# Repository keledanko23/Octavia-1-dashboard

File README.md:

# Octavia-1-Dashboard

A dashboard project.

## 📋 Project Overview

This is the Octavia-1 Dashboard - a comprehensive dashboard solution designed to use for pc simulators.
I have significantly expanded the scope of this project into a multi-phase hardware and software engineering build. I am converting a physical Skoda Octavia MK1 instrument cluster into a high-fidelity, real-time PC flight/racing simulator telemetry display.

## Current Progress (73 Hours Logged):

Hardware Reverse Engineering: Analyzed the internal trace lines, power rail limits, and motor pinouts of a replacement cluster following a previous hardware       failure (which was an excellent learning experience).
Interface Board Fabrication: Built a fully functional hardware interface on a 5x7cm barna perfboard, permanently soldering 3 driver ICs to safely handle logic     signal conversions between the microcontroller and the dashboard.
Complex Wire Harnessing: Engineered a point-to-point jumper wire harness to break out the connections. Applied hot-melt adhesive to insulate exposed solder        joints and provide mechanical strain relief.
Finished PCB design

## Remaining Scope:

Firmware Development: Writing custom python code using tkinter to simulate how it should work
Custom PCB Shield Design: Try to create a pcb for it.

## Diary

### 1st log (3.5 hours)
Analyzed the internal board layout of the replacement cluster. Traced the circuit lines to find the correct entry points for the stepper motors and indicators to avoid another hardware failure.
  ### Disassembly

  ### LEDS

  ### Pinout

## 2nd log (4 hours)
Mapped out the component placement on the 5x7cm barna perfboard. Positioned the three driver ICs and the male headers, then permanently soldered them onto the prototype board.

  ### ICs

## 3rd log (4.5 hours)
Started building the complex point-to-point jumper wire harness. Stripped, routed, and soldered individual wires from the IC legs to the breakout headers to safely transfer signals.

  ### Wires

## 4th log (4 hours)
Used a multimeter to test continuity on every single soldered connection. Checked for accidental solder bridges between the IC pins to prevent any short circuits before testing on live power.
 
  ### Checking

## 5th log (4 hours)
Completed the hardware prototyping phase. Applied layers of hot-melt adhesive over the wire cluster to insulate the exposed solder joints and provide mechanical strain relief against loose connections.

  ### Coating

## 6th log (5 hours)
Completed a simulation python code that shows how it will work.

  ### Python screenshot

  ## DEMO LINK: https://youtu.be/50QhlQHXBYw

  ## PYTHON CODE [HERE](https://github.com/keledanko23/Octavia-1-dashboard/blob/main/Octavia%20mk1%20dashboard%20python%20code.py)
  
  ## 7th log(2.5 hours)
  Started mapping out the pcb so i can recreate it later, added 1more led to the prototype, tried to add 2more but they burned out

  ## 8th log(9.2 hours)
  Started building the pcb outlines and holes, unfortunatly lot of the holes arent on their places where they should be even if i mesure 10 times, at least the outline is finally the form i need and some of the holes ar on their places.

## 9th log(3.7 hours)
Finaly got a chance to use a scaner to scan the pcb, imported it into kicad ad fixed al the kholes location and the form of the pcb, the pcb form is now finished

## 10th log(7 hours)
Drawed the schematic, it was really hard because I did not find some IC-s and had to draw them myself, at first it had 56errors but i managed to fix it

## 11th log(9 hours)
Added the components and conected most of the traces but I can´t make it cleaner, and i ran the DRC it said it has 250 errors and 110 alerts so i have a lot of work to do.

## 12th log(9.2 hours)
Fixed the layout, changed some expensive IC-s to cheaper ones, almost finished

## 13th log(5.8 hours)
Finally finished the pcb, it´s ready for order

## PCB FILES [HERE](https://github.com/keledanko23/Octavia-1-dashboard/tree/main/PCB%20FILES)

## [BOM IN TABLE FOMRAT](https://docs.google.com/spreadsheets/d/1glcknnUEBRp5D3enFJscNNNqzlTzyaNK3k0CQGIx504/edit?usp=sharing)

## 14th log(10,9 hours)
I soldered on evrything and foun out i got scammed and the ics from aliexpress were fake so i had to order new ones and found out my board had some issues so i will fix it in kicad
It is finished
## DEMO LINK: https://youtu.be/WoHd4EV55U8
**Last Updated:** October 30, 2026

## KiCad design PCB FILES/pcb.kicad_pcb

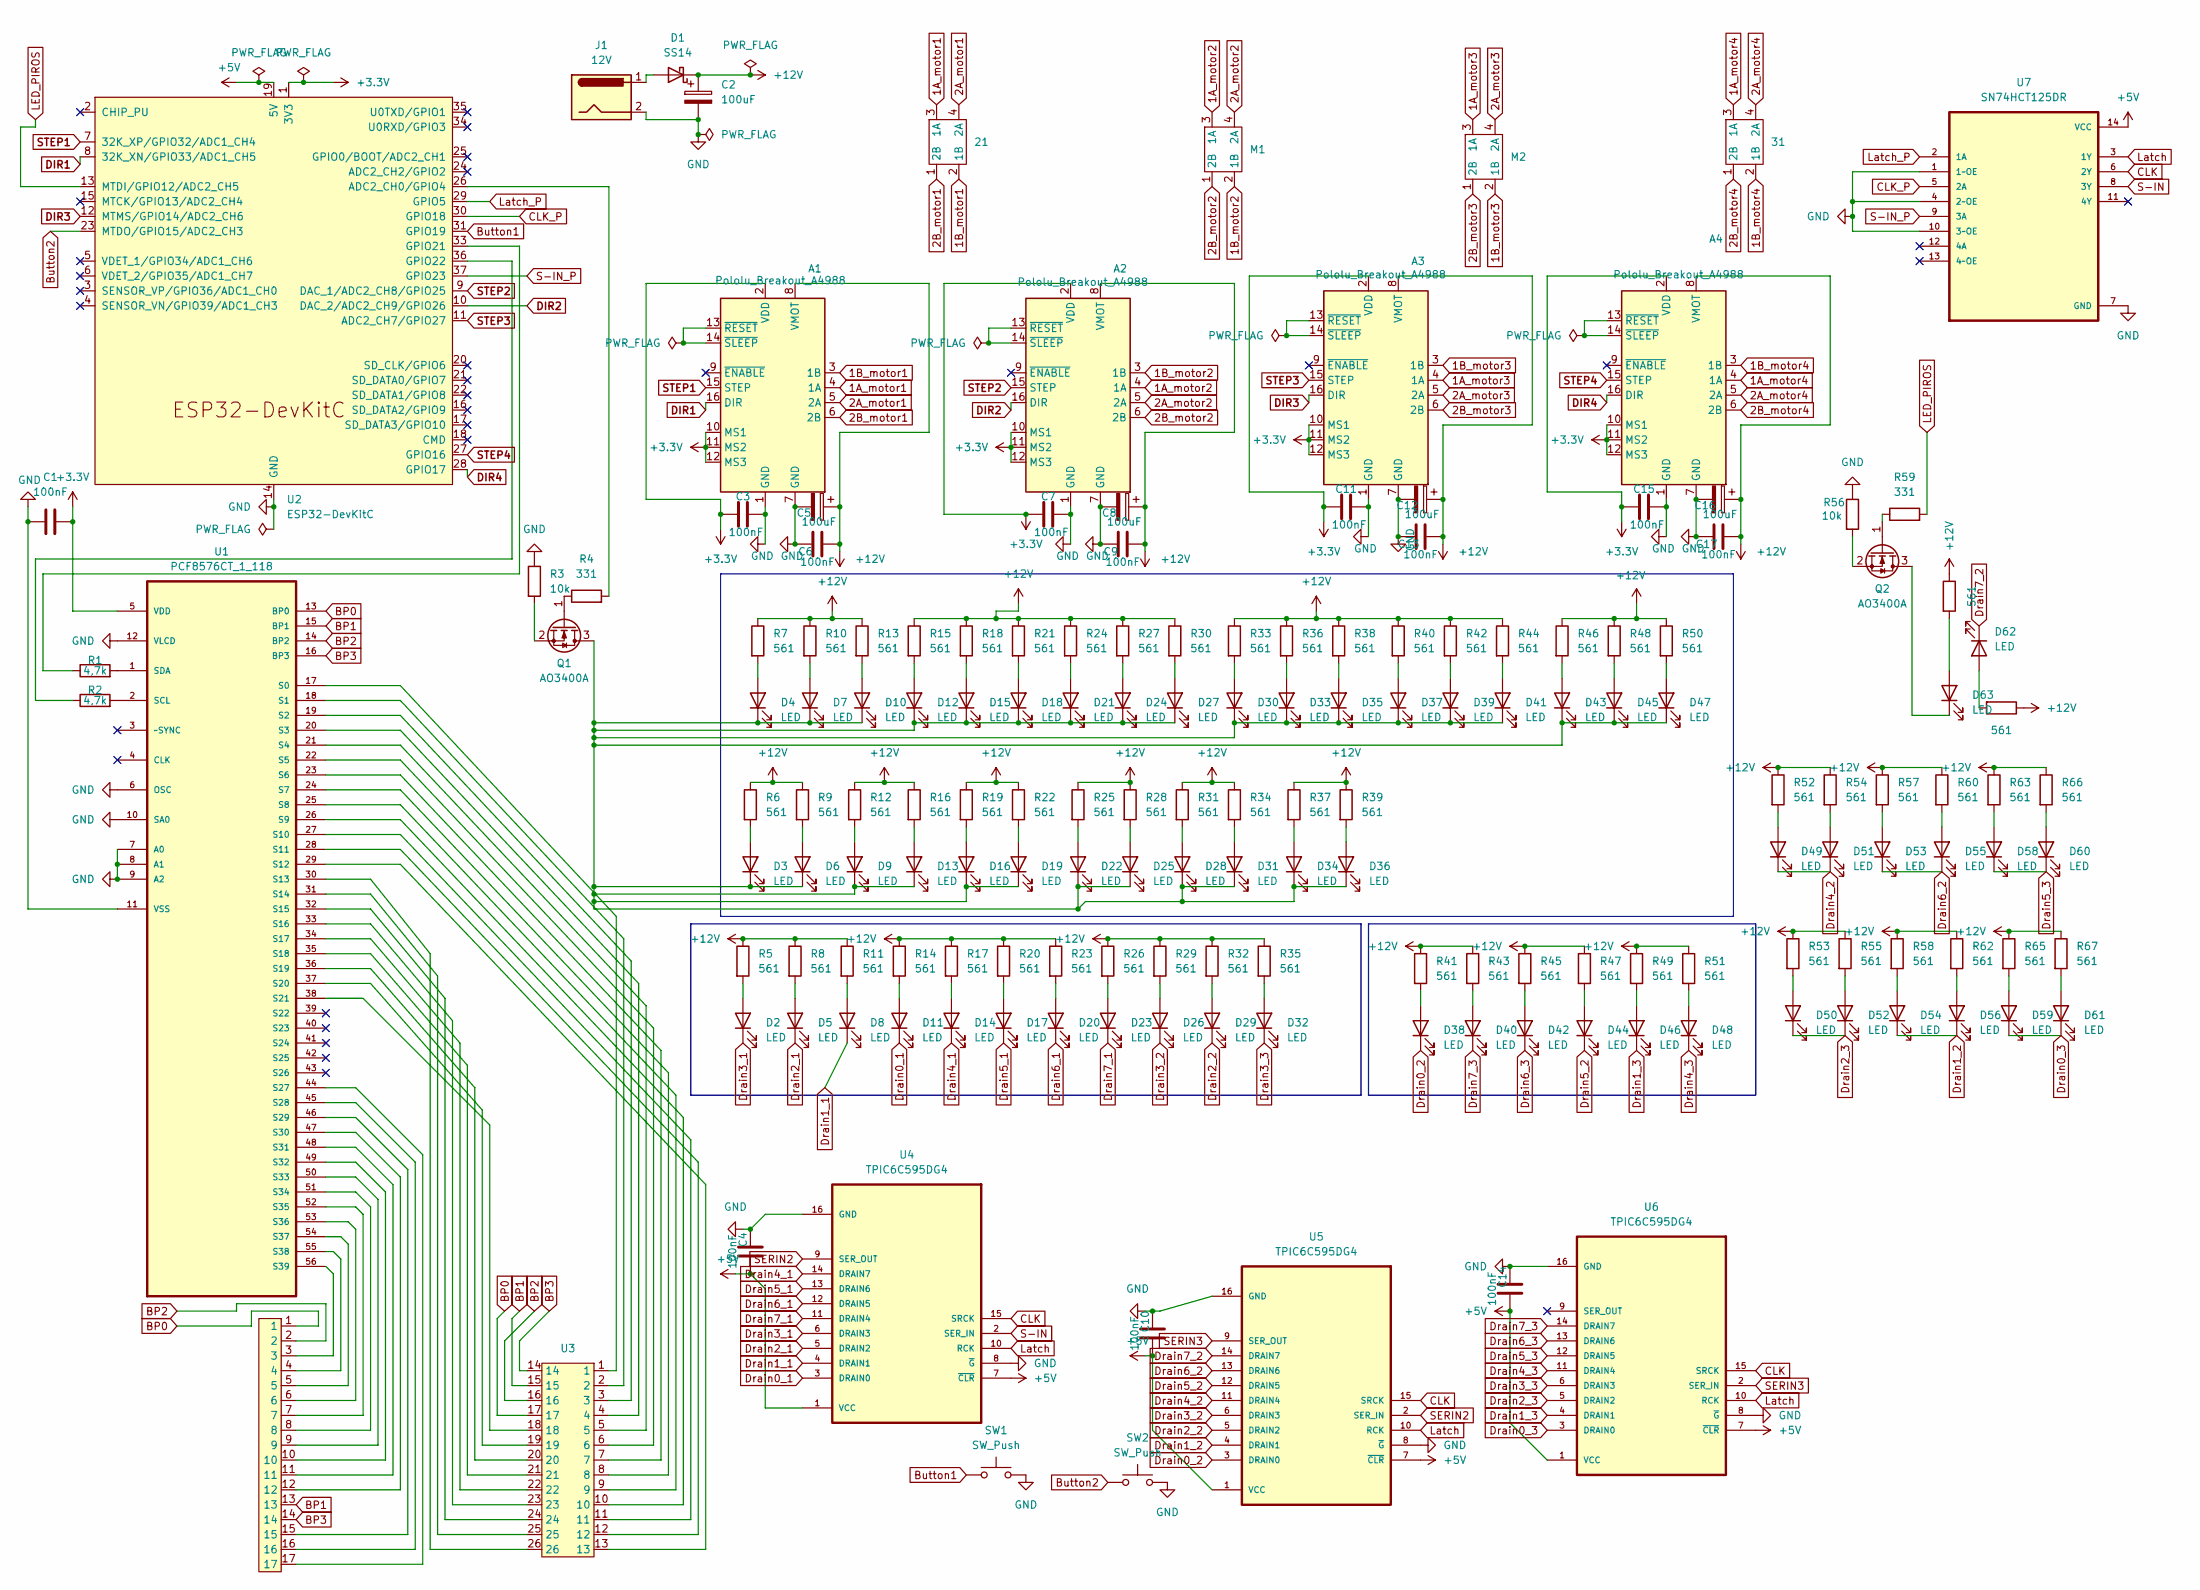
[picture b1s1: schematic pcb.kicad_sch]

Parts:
11: LCDPADS_LEFT1
21, 31: Bez názvu
A1, A2, A3, A4: Pololu_Breakout_A4988; Pololu_Breakout-16_15.2x20.3mm
C1, C3, C4, C6, C7, C9, C10, C11, C13, C14, C15, C17: 100nF; C_0805_2012Metric_Pad1.18x1.45mm_HandSolder
C2, C5, C8, C12, C16: 100uF; C_Elec_6.3x7.7
D1: SS14; D_DO-15_P10.16mm_Horizontal
D2, D3, D4, D5, D6, D7, D8, D9, D10, D11, D12, D13, D14, D15, D16, D17, D18, D19, D20, D21, D22, D23, D24, D25, D26, D27, D28, D29, D30, D31, D32, D33, D34, D35, D36, D37, D38, D39, D40, D41, D42, D43, D44, D45, D46, D47, D48, D49, D50, D51, D52, D53, D54, D55, D56, D58, D59, D60, D61, D62, D63: LED; LED_PLCC_2835_Handsoldering
J1: 12V; BarrelJack_Horizontal
M1, M2: Bez názvu
Q1, Q2: AO3400A; SOT-23_Handsoldering
R1, R2: 4,7k; R_0805_2012Metric_Pad1.20x1.40mm_HandSolder
R3, R56: 10k; R_0805_2012Metric_Pad1.20x1.40mm_HandSolder
R4, R59: 331; R_0805_2012Metric_Pad1.20x1.40mm_HandSolder
R5, R6, R7, R8, R9, R10, R11, R12, R13, R14, R15, R16, R17, R18, R19, R20, R21, R22, R23, R24, R25, R26, R27, R28, R29, R30, R31, R32, R33, R34, R35, R36, R37, R38, R39, R40, R41, R42, R43, R44, R45, R46, R47, R48, R49, R50, R51, R52, R53, R54, R55, R57, R58, R60, R62, R63, R64, R65, R66, R67, R68: 561; R_0805_2012Metric_Pad1.20x1.40mm_HandSolder
SW1, SW2: SW_Push; Bez názvu
U1: PCF8576CT_1_118; PCFCHIP; MPN PCF8576CT/1,118
U2: ESP32-DevKitC
U3: LCDPADS_RIGHT1
U4, U5, U6: TPIC6C595DG4; SOIC127P600X175-16N
U7: SN74HCT125DR; DIP-14_W7.62mm

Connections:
1A_motor1: 21.3 (1A), A1.4 (1A)
1A_motor2: A2.4 (1A), M1.3 (1A)
1A_motor3: A3.4 (1A), M2.3 (1A)
1A_motor4: 31.3 (1A), A4.4 (1A)
1B_motor1: 21.2 (1B), A1.3 (1B)
1B_motor2: A2.3 (1B), M1.2 (1B)
1B_motor3: A3.3 (1B), M2.2 (1B)
1B_motor4: 31.2 (1B), A4.3 (1B)
2A_motor1: 21.4 (2A), A1.5 (2A)
2A_motor2: A2.5 (2A), M1.4 (2A)
2A_motor3: A3.5 (2A), M2.4 (2A)
2A_motor4: 31.4 (2A), A4.5 (2A)
2B_motor1: 21.1 (2B), A1.6 (2B)
2B_motor2: A2.6 (2B), M1.1 (2B)
2B_motor3: A3.6 (2B), M2.1 (2B)
2B_motor4: 31.1 (2B), A4.6 (2B)
+3.3V: A1.2 (VDD), A1.10 (MS1), A1.11 (MS2), A1.12 (MS3), A2.2 (VDD), A2.10 (MS1), A2.11 (MS2), A2.12 (MS3), A3.2 (VDD), A3.10 (MS1), A3.11 (MS2), A3.12 (MS3), A4.2 (VDD), A4.10 (MS1), A4.11 (MS2), A4.12 (MS3), C1.2, C3.1, C7.1, C11.1, C15.1, U1.5 (VDD), U2.1 (3V3)
+5V: C4.2, C10.2, C14.2, U2.19 (5V), U4.1 (VCC), U4.7 (~CLR), U5.1 (VCC), U5.7 (~CLR), U6.1 (VCC), U6.7 (~CLR), U7.14 (VCC)
+12V: A1.8 (VMOT), A2.8 (VMOT), A3.8 (VMOT), A4.8 (VMOT), C2.1, C5.1, C6.2, C8.1, C9.2, C12.1, C13.2, C16.1, C17.2, D1.1 (K), R5.1, R6.1, R7.1, R8.1, R9.1, R10.1, R11.1, R12.1, R13.1, R14.1, R15.1, R16.1, R17.1, R18.1, R19.1, R20.1, R21.1, R22.1, R23.1, R24.1, R25.1, R26.1, R27.1, R28.1, R29.1, R30.1, R31.1, R32.1, R33.1, R34.1, R35.1, R36.1, R37.1, R38.1, R39.1, R40.1, R41.1, R42.1, R43.1, R44.1, R45.1, R46.1, R47.1, R48.1, R49.1, R50.1, R51.1, R52.1, R53.1, R54.1, R55.1, R57.1, R58.1, R60.1, R62.1, R63.1, R64.1, R65.1, R66.1, R67.1, R68.1
BP0: 11.1, U1.13 (BP0), U3.17
BP1: 11.13, U1.15 (BP1), U3.15
BP2: 11.2, U1.14 (BP2), U3.16
BP3: 11.14, U1.16 (BP3), U3.14
Button1: SW1.1, U2.31 (GPIO19)
Button2: SW2.1, U2.23 (MTDO/GPIO15/ADC2_CH3)
CLK: U4.15 (SRCK), U5.15 (SRCK), U6.15 (SRCK), U7.6 (2Y)
CLK_P: U2.30 (GPIO18), U7.5 (2A)
DIR1: A1.16 (DIR), U2.8 (32K_XN/GPIO33/ADC1_CH5)
DIR2: A2.16 (DIR), U2.10 (DAC_2/ADC2_CH9/GPIO26)
DIR3: A3.16 (DIR), U2.12 (MTMS/GPIO14/ADC2_CH6)
DIR4: A4.16 (DIR), U2.28 (GPIO17)
Drain0_1: D11.1 (K), U4.3 (DRAIN0)
Drain0_2: D38.1 (K), U5.3 (DRAIN0)
Drain0_3: D59.1 (K), D61.1 (K), U6.3 (DRAIN0)
Drain1_1: D8.1 (K), U4.4 (DRAIN1)
Drain1_2: D54.1 (K), D56.1 (K), U5.4 (DRAIN1)
Drain1_3: D46.1 (K), U6.4 (DRAIN1)
Drain2_1: D5.1 (K), U4.5 (DRAIN2)
Drain2_2: D29.1 (K), U5.5 (DRAIN2)
Drain2_3: D50.1 (K), D52.1 (K), U6.5 (DRAIN2)
Drain3_1: D2.1 (K), U4.6 (DRAIN3)
Drain3_2: D26.1 (K), U5.6 (DRAIN3)
Drain3_3: D32.1 (K), U6.6 (DRAIN3)
Drain4_1: D14.1 (K), U4.14 (DRAIN7)
Drain4_2: D49.1 (K), D51.1 (K), U5.11 (DRAIN4)
Drain4_3: D48.1 (K), U6.11 (DRAIN4)
Drain5_1: D17.1 (K), U4.13 (DRAIN6)
Drain5_2: D44.1 (K), U5.12 (DRAIN5)
Drain5_3: D58.1 (K), D60.1 (K), U6.12 (DRAIN5)
Drain6_1: D20.1 (K), U4.12 (DRAIN5)
Drain6_2: D53.1 (K), D55.1 (K), U5.13 (DRAIN6)
Drain6_3: D42.1 (K), U6.13 (DRAIN6)
Drain7_1: D23.1 (K), U4.11 (DRAIN4)
Drain7_2: D62.1 (K), U5.14 (DRAIN7)
Drain7_3: D40.1 (K), U6.14 (DRAIN7)
GND: A1.1 (GND), A1.7 (GND), A2.1 (GND), A2.7 (GND), A3.1 (GND), A3.7 (GND), A4.1 (GND), A4.7 (GND), C1.1, C2.2, C3.2, C4.1, C5.2, C6.1, C7.2, C8.2, C9.1, C10.1, C11.2, C12.2, C13.1, C14.1, C15.2, C16.2, C17.1, J1.2, R3.1, R56.1, SW1.2, SW2.2, U1.6 (OSC), U1.7 (A0), U1.8 (A1), U1.9 (A2), U1.10 (SA0), U1.11 (VSS), U1.12 (VLCD), U2.14 (GND), U2.32 (GND), U2.38 (GND), U4.8 (~G), U4.16 (GND), U5.8 (~G), U5.16 (GND), U6.8 (~G), U6.16 (GND), U7.1 (1~OE), U7.4 (2~OE), U7.7 (GND), U7.10 (3~OE)
LED_PIROS: R59.2, U2.13 (MTDI/GPIO12/ADC2_CH5)
Latch: U4.10 (RCK), U5.10 (RCK), U6.10 (RCK), U7.3 (1Y)
Latch_P: U2.29 (GPIO5), U7.2 (1A)
unnamed: A1.13 (~RESET), A1.14 (~SLEEP)
unnamed: A2.13 (~RESET), A2.14 (~SLEEP)
unnamed: A3.13 (~RESET), A3.14 (~SLEEP)
unnamed: A4.13 (~RESET), A4.14 (~SLEEP)
unnamed: D1.2 (A), J1.1
unnamed: D2.2 (A), R5.2
unnamed: D3.2 (A), R6.2
unnamed: D4.2 (A), R7.2
unnamed: D5.2 (A), R8.2
unnamed: D6.2 (A), R9.2
unnamed: D7.2 (A), R10.2
unnamed: D8.2 (A), R11.2
unnamed: D9.2 (A), R12.2
unnamed: D10.2 (A), R13.2
unnamed: D3.1 (K), D4.1 (K), D6.1 (K), D7.1 (K), D9.1 (K), D10.1 (K), D12.1 (K), D13.1 (K), D15.1 (K), D16.1 (K), D18.1 (K), D19.1 (K), D21.1 (K), D22.1 (K), D24.1 (K), D25.1 (K), D27.1 (K), D28.1 (K), D30.1 (K), D31.1 (K), D33.1 (K), D34.1 (K), D35.1 (K), D36.1 (K), D37.1 (K), D39.1 (K), D41.1 (K), D43.1 (K), D45.1 (K), D47.1 (K), Q1.3 (D)
unnamed: D11.2 (A), R14.2
unnamed: D12.2 (A), R15.2
unnamed: D13.2 (A), R16.2
unnamed: D14.2 (A), R17.2
unnamed: D15.2 (A), R18.2
unnamed: D16.2 (A), R19.2
unnamed: D17.2 (A), R20.2
unnamed: D18.2 (A), R21.2
unnamed: D19.2 (A), R22.2
unnamed: D20.2 (A), R23.2
unnamed: D21.2 (A), R24.2
unnamed: D22.2 (A), R25.2
unnamed: D23.2 (A), R26.2
unnamed: D24.2 (A), R27.2
unnamed: D25.2 (A), R28.2
unnamed: D26.2 (A), R29.2
unnamed: D27.2 (A), R30.2
unnamed: D28.2 (A), R31.2
unnamed: D29.2 (A), R32.2
unnamed: D30.2 (A), R33.2
unnamed: D31.2 (A), R34.2
unnamed: D32.2 (A), R35.2
unnamed: D33.2 (A), R36.2
unnamed: D34.2 (A), R37.2
unnamed: D35.2 (A), R38.2
unnamed: D36.2 (A), R39.2
unnamed: D37.2 (A), R40.2
unnamed: D38.2 (A), R41.2
unnamed: D39.2 (A), R42.2
unnamed: D40.2 (A), R43.2
unnamed: D41.2 (A), R44.2
unnamed: D42.2 (A), R45.2
unnamed: D43.2 (A), R46.2
unnamed: D44.2 (A), R47.2
unnamed: D45.2 (A), R48.2
unnamed: D46.2 (A), R49.2
unnamed: D47.2 (A), R50.2
unnamed: D48.2 (A), R51.2
unnamed: D49.2 (A), R52.2
unnamed: D50.2 (A), R53.2
unnamed: D51.2 (A), R54.2
unnamed: D52.2 (A), R55.2
unnamed: D53.2 (A), R57.2
unnamed: D54.2 (A), R58.2
unnamed: D55.2 (A), R60.2
unnamed: D56.2 (A), R62.2
unnamed: D58.2 (A), R63.2
unnamed: D59.2 (A), R65.2
unnamed: D60.2 (A), R66.2
unnamed: D61.2 (A), R67.2
unnamed: D62.2 (A), R64.2
unnamed: D63.2 (A), R68.2
unnamed: D63.1 (K), Q2.3 (D)
unnamed: Q1.1 (G), R4.1
unnamed: Q1.2 (S), R3.2
unnamed: Q2.1 (G), R59.1
unnamed: Q2.2 (S), R56.2
unnamed: U1.17 (S0), U3.1
unnamed: U1.18 (S1), U3.2
unnamed: U1.19 (S2), U3.3
unnamed: U1.20 (S3), U3.4
unnamed: U1.21 (S4), U3.5
unnamed: U1.22 (S5), U3.6
unnamed: U1.23 (S6), U3.7
unnamed: U1.24 (S7), U3.8
unnamed: U1.25 (S8), U3.9
unnamed: U1.26 (S9), U3.10
unnamed: U1.27 (S10), U3.11
unnamed: U1.28 (S11), U3.12
unnamed: U1.29 (S12), U3.13
unnamed: U1.30 (S13), U3.26
unnamed: U1.31 (S14), U3.25
unnamed: U1.32 (S15), U3.24
unnamed: U1.33 (S16), U3.23
unnamed: U1.34 (S17), U3.22
unnamed: U1.35 (S18), U3.21
unnamed: U1.36 (S19), U3.20
unnamed: U1.37 (S20), U3.19
unnamed: U1.38 (S21), U3.18
unnamed: 11.17, U1.44 (S27)
unnamed: 11.16, U1.45 (S28)
unnamed: 11.15, U1.46 (S29)
unnamed: 11.12, U1.47 (S30)
unnamed: 11.11, U1.48 (S31)
unnamed: 11.10, U1.49 (S32)
unnamed: 11.9, U1.50 (S33)
unnamed: 11.8, U1.51 (S34)
unnamed: 11.7, U1.52 (S35)
unnamed: 11.6, U1.53 (S36)
unnamed: 11.5, U1.54 (S37)
unnamed: 11.4, U1.55 (S38)
unnamed: 11.3, U1.56 (S39)
unnamed: R2.2, U1.2 (SCL)
unnamed: R1.2, U1.1 (SDA)
unnamed: R4.2, U2.26 (ADC2_CH0/GPIO4)
unnamed: R1.1, U2.33 (GPIO21)
unnamed: R2.1, U2.36 (GPIO22)
S-IN: U4.2 (SER_IN), U7.8 (3Y)
S-IN_P: U2.37 (GPIO23), U7.9 (3A)
SERIN2: U4.9 (SER_OUT), U5.2 (SER_IN)
SERIN3: U5.9 (SER_OUT), U6.2 (SER_IN)
STEP1: A1.15 (STEP), U2.7 (32K_XP/GPIO32/ADC1_CH4)
STEP2: A2.15 (STEP), U2.9 (DAC_1/ADC2_CH8/GPIO25)
STEP3: A3.15 (STEP), U2.11 (ADC2_CH7/GPIO27)
STEP4: A4.15 (STEP), U2.27 (GPIO16)

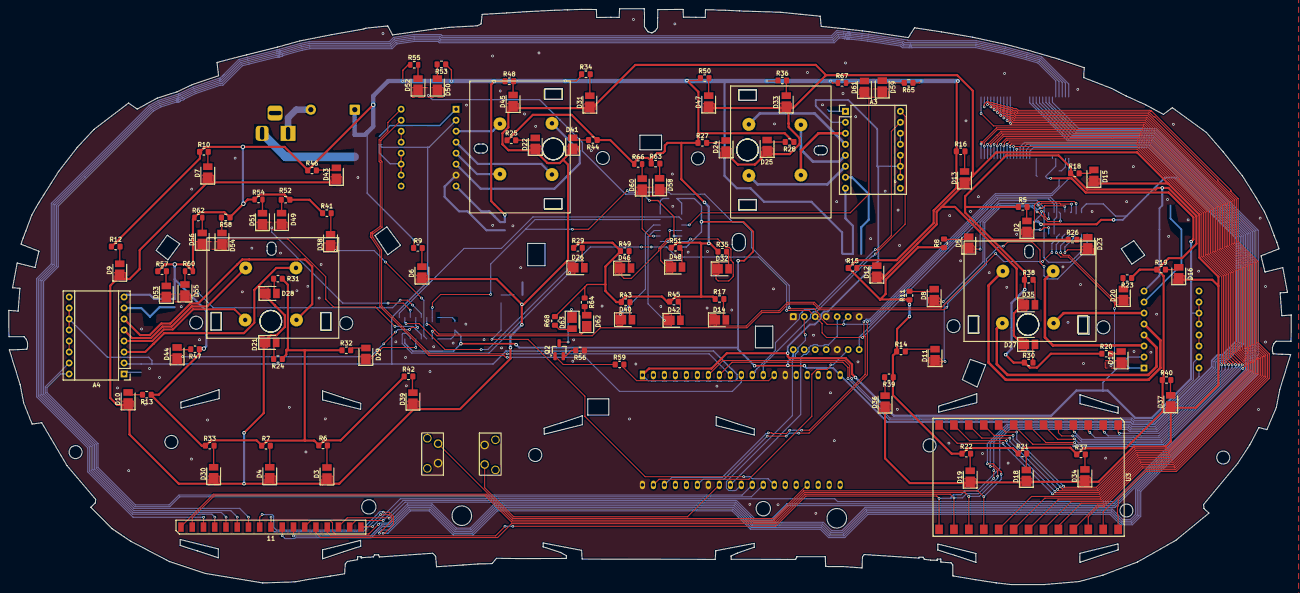
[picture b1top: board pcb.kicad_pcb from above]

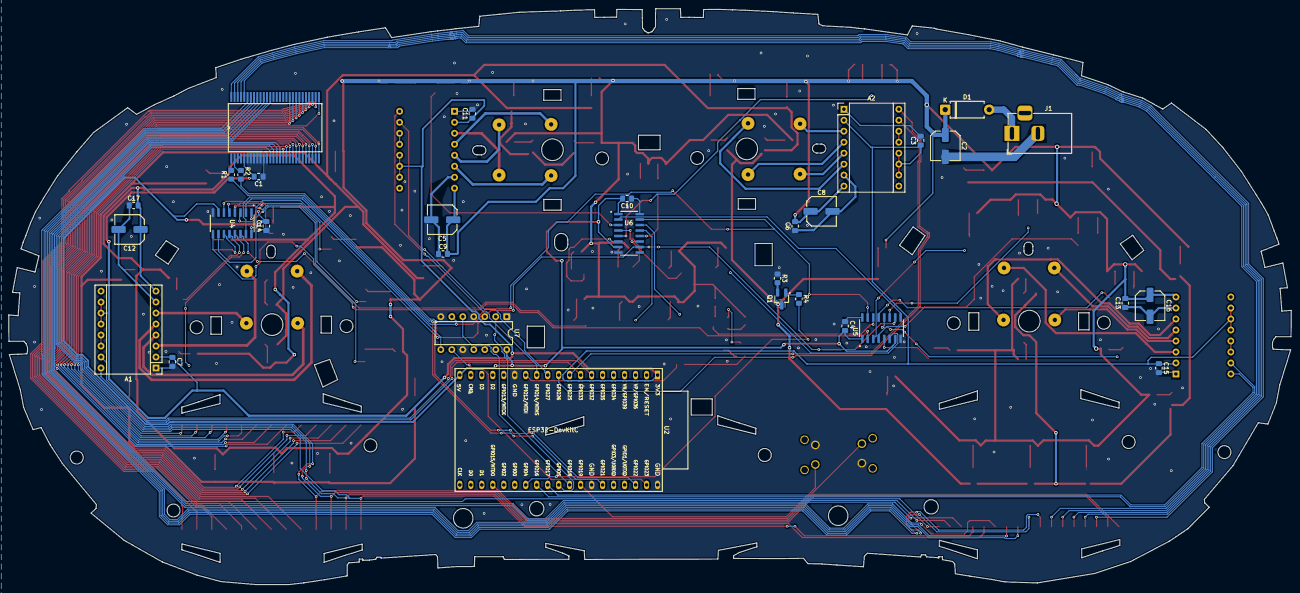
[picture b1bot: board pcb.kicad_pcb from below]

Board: 2 copper layers, 296.5 x 133.1 mm, 167 parts (32 on the bottom side), 179 nets.

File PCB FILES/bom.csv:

Designator,Footprint,Quantity,Value,LCSC Part #
11,LCDPADS_LEFT1,1,~,
"21, 31, M1, M2",Bez názvu,4,~,
"A1, A2, A3, A4",Pololu_Breakout-16_15.2x20.3mm,4,Pololu_Breakout_A4988,
"C1, C10, C11, C13, C14, C15, C17, C3, C4, C6, C7, C9",0805,12,100nF,
"C12, C16, C2, C5, C8",C_Elec_6.3x7.7,5,100uF,
D1,D_DO-15_P10.16mm_Horizontal,1,SS14,
"D10, D11, D12, D13, D14, D15, D16, D17, D18, D19, D2, D20, D21, D22, D23, D24, D25, D26, D27, D28, D29, D3, D30, D31, D32, D33, D34, D35, D36, D37, D38, D39, D4, D40, D41, D42, D43, D44, D45, D46, D47, D48, D49, D5, D50, D51, D52, D53, D54, D55, D56, D58, D59, D6, D60, D61, D62, D63, D7, D8, D9",LED_PLCC_2835_Handsoldering,61,LED,
J1,BarrelJack_Horizontal,1,12V,
"Q1, Q2",SOT-23_Handsoldering,2,AO3400A,
"R1, R2",0805,2,"4,7k",
"R10, R11, R12, R13, R14, R15, R16, R17, R18, R19, R20, R21, R22, R23, R24, R25, R26, R27, R28, R29, R30, R31, R32, R33, R34, R35, R36, R37, R38, R39, R40, R41, R42, R43, R44, R45, R46, R47, R48, R49, R5, R50, R51, R52, R53, R54, R55, R57, R58, R6, R60, R62, R63, R64, R65, R66, R67, R68, R7, R8, R9",0805,61,561,
"R3, R56",0805,2,10k,
"R4, R59",0805,2,331,
"SW1, SW2",Bez názvu,2,SW_Push,
U1,PCFCHIP,1,PCF8576CT_1_118,"PCF8576CT/1,118"
U2,ESP32-DevKitC,1,ESP32-DevKitC,
U3,LCDPADS_RIGHT1,1,~,
"U4, U5, U6",SOIC127P600X175-16N,3,TPIC6C595DG4,
U7,DIP-14_W7.62mm,1,SN74HCT125DR,

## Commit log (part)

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2026-05-30 Initial commit: Add README with project template
2026-05-30 Revise README with new project details and diary
    Updated project description and added diary entry.
2026-05-30 images.png
2026-05-30 Add sized dashboard images (disassembly and figuring out) to README
2026-05-30 Revise README content and update last updated date
    Updated project description and image references in README.md.
2026-06-21 Update README with simulation code and new date
    Added details about the simulation Python code and updated the last updated date.
